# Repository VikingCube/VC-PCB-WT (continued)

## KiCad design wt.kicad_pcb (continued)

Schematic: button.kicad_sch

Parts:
C11: C-100nF-0805; C_0805_2012Metric_Pad1.18x1.45mm_HandSolder
R30: R-100-0603; R_0603_1608Metric
R31: R-10k-0603; R_0603_1608Metric_Pad0.98x0.95mm_HandSolder
SW2: SW_Push; SW_PUSH_6mm_H9.5mm

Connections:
+3.3VA: R31.1; also elsewhere on the board
BTN0: C11.1, R30.2; also elsewhere on the board
GND3: C11.2, SW2.2; also elsewhere on the board
unnamed: R30.1, R31.2, SW2.1

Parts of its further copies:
C10, C12, C13, C14, C15: C-100nF-0805; C_0805_2012Metric_Pad1.18x1.45mm_HandSolder
R13, R38, R40, R42, R44: R-100-0603; R_0603_1608Metric
R14, R39, R41, R43, R45: R-10k-0603; R_0603_1608Metric_Pad0.98x0.95mm_HandSolder
SW1, SW3, SW4, SW5, SW6: SW_Push; SW_PUSH_6mm_H9.5mm

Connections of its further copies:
+3.3VA: R14.1, R39.1, R41.1, R43.1, R45.1; also elsewhere on the board
BTN1: C10.1, R13.2; also elsewhere on the board
BTN2: C12.1, R38.2; also elsewhere on the board
BTN3: C13.1, R40.2; also elsewhere on the board
BTN4: C14.1, R42.2; also elsewhere on the board
BTN5: C15.1, R44.2; also elsewhere on the board
GND3: C10.2, C12.2, C13.2, C14.2, C15.2, SW1.2, SW3.2, SW4.2, SW5.2, SW6.2; also elsewhere on the board
unnamed: R13.1, R14.2, SW1.1
unnamed: R38.1, R39.2, SW3.1
unnamed: R40.1, R41.2, SW4.1
unnamed: R42.1, R43.2, SW5.1
unnamed: R44.1, R45.2, SW6.1

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
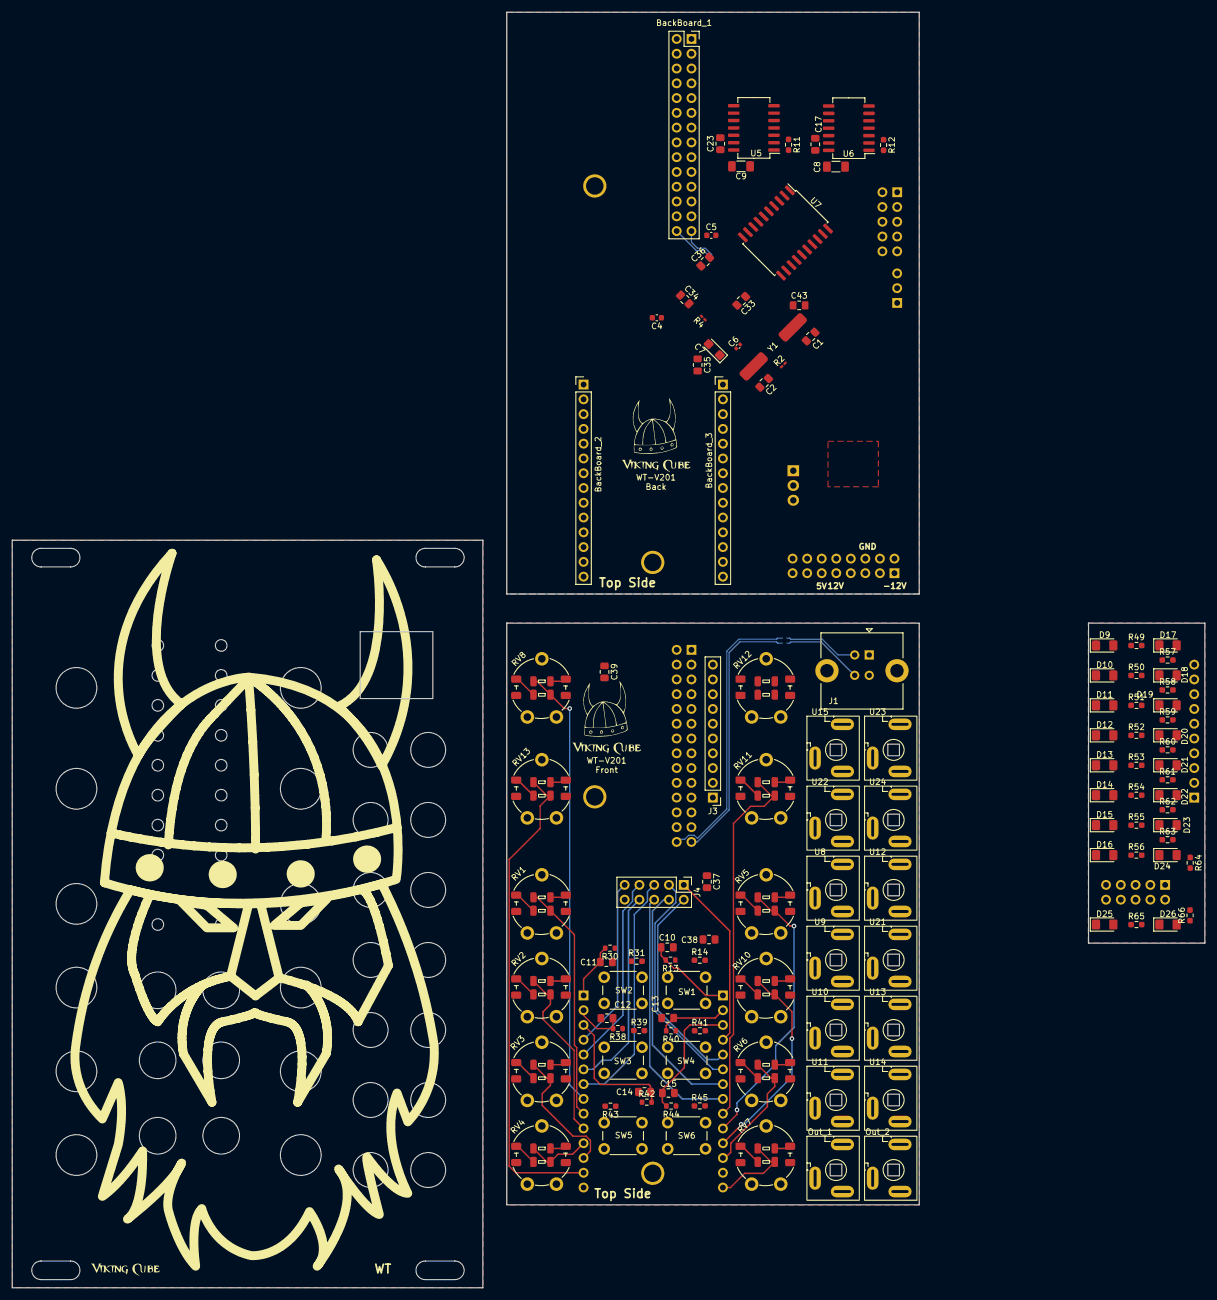
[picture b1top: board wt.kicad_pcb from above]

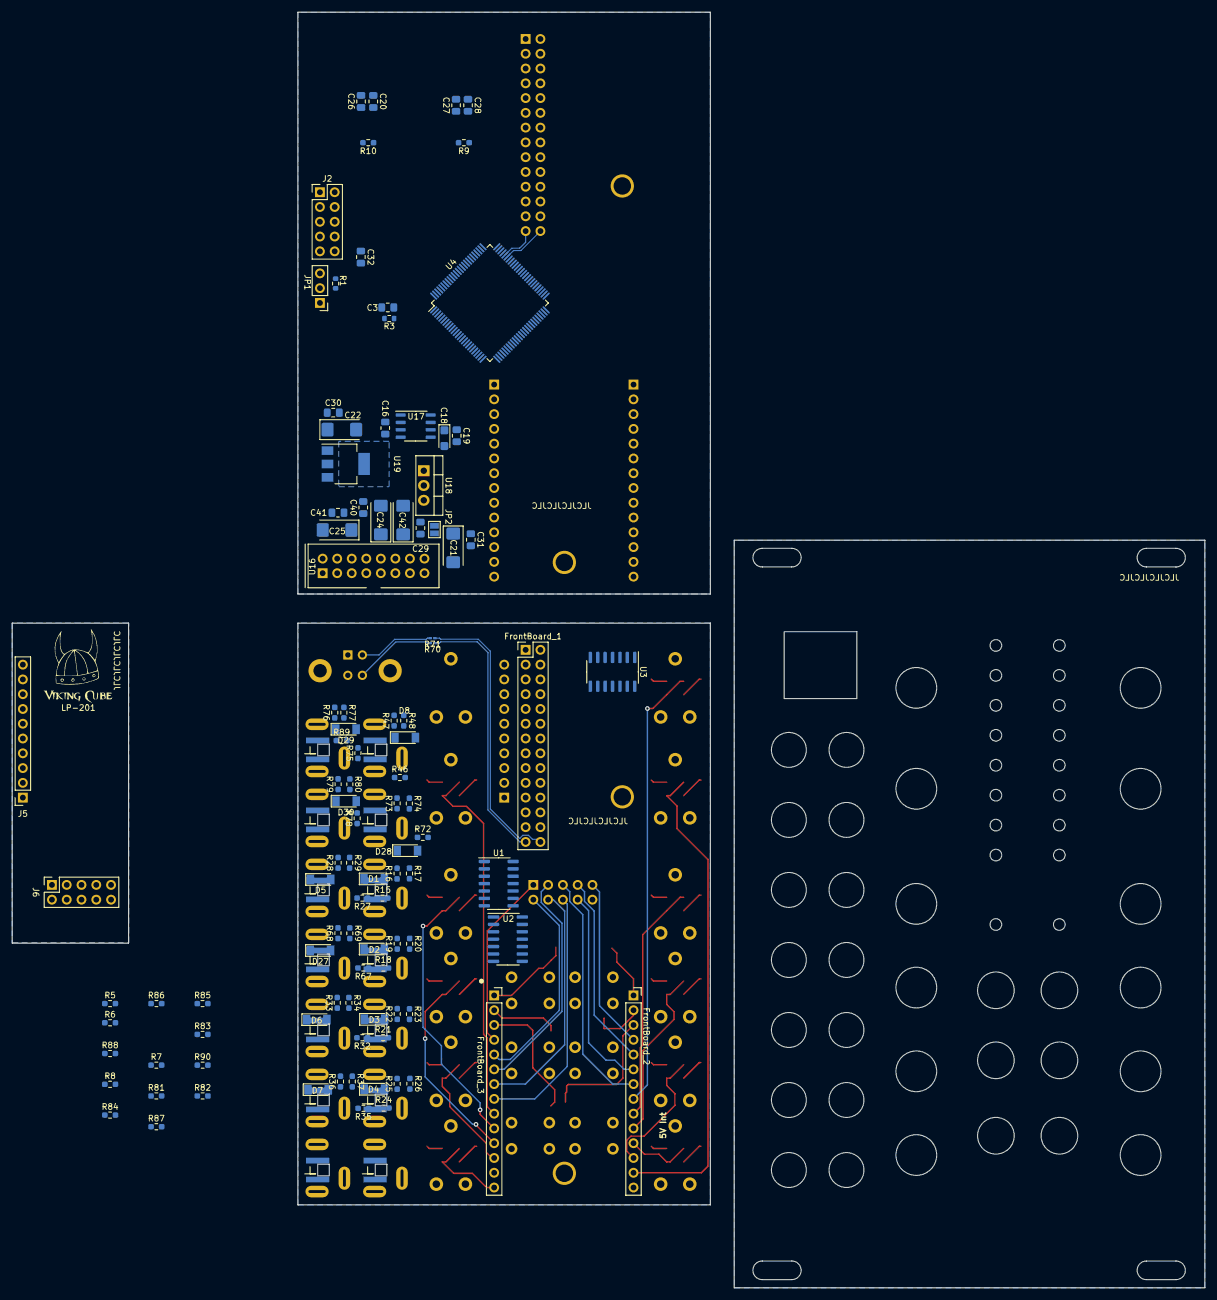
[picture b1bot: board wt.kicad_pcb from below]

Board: 4 copper layers, 205.0 x 219.2 mm, 286 parts (104 on the bottom side), 296 nets.

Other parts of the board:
FP3, FP4, FP5, FP6, FP7, FP8, FP32, FP33, FP34, FP35, FP36, FP37: mount_Potentiometer_Piher_PT-10-V10_Vertical
FP9, FP10, FP11, FP12, FP13, FP14, FP15, FP15#2, FP17#2, FP20, FP21, FP22, FP23, FP24, FP25, FP26, FP27, FP28: mount_m2
FP17, FP18, FP19, FP29, FP30, FP31: mount_SW_PUSH_6mm_H9.5mm
FP38, FP39, FP40, FP41, FP42, FP43, FP44, FP45, FP46, FP47, FP48, FP49, FP50, FP51: mount_LUM_1502-03
FP54: mount_USB-BG
FP55: JLCPCB-TAG
G011: LOGO; logo_small
LOGO: logo_head
Mount4: mount_m3_pad
Mount_1, Mount_2: mount_m3_pad
REF123: JLCPCB-TAG
TEXT1, TEXT2: JLCPCB-TAG
mount3: mount_m3_pad
mount_1, mount_2, mount_3, mount_4: mounting

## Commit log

2022-07-29 First
2022-07-29 working on the schema
2022-07-29 started to work on power part
2022-07-31 working on powers
2022-07-31 refactoring with global labels
2022-08-01 cleaning into modules
2022-08-02 Working on the limiter
2022-08-03 working on AD inputs
2022-08-04 re-thinked the controls
2022-08-04 added some missing wires, whoopppssssz
2022-08-04 reannotated changed to LM324
2022-08-04 almost messed up the opamp :)
2022-08-05 Made the first proposed layout
2022-08-14 working on the PCB
2022-08-14 working on PCB
2022-08-15 PCV WIP
2022-08-15 fixed aligments - check again
2022-08-20 working on PCB, new iteratrion
2022-08-30 Working on the PCB / JTAG
2022-09-01 started to pull GND
2022-09-01 shall be error free, proceeding to warnings
2022-09-01 no more warnings making it nicer
2022-09-01 Added the logo
2022-09-01 Added some labels
2022-09-05 final touches
2022-09-27 reworking with Pot Lights
2022-09-30 fixed issues, power still needs to be addressed
2022-10-04 New design
2022-10-09 working on the new pcb
2022-10-10 working on PCB v2 LEDs
2022-10-10 using power plane as signal too - will this fly?
2022-10-10 Moved around a lot, I think we close to GND phase
2022-10-11 Getting into GND-ing
2022-10-12 grounding
2022-10-14 v2 error free
2022-10-14 V2.0 final
2022-10-14 Working on the cover
2022-10-18 working on lifted leds
2022-10-18 wip led panel
2022-10-18 working on v3 - todo go on with power lines
2022-10-18 wip - go btn
2022-10-21 working on the v3 leds
2022-10-21 woking on the LEDs
2022-10-26 yet an other new version with 3 boards
2022-10-26 this will be a monster
2022-10-27 working on v3 - so far so good
2022-10-27 wip v3
2022-10-31 v4 error free
2022-10-31 v4 grounding
2022-10-31 Final V4, no cover
2022-10-31 V4 cover wip
2022-10-31 V4 with Cover, final?
2022-10-31 V4 - Final
2022-10-31 removed other panels
2022-10-31 fixed jlc tag
2022-11-17 fixed button hole size on front panel
2022-11-25 updated readme.
2022-11-26 fixed hole sizes
2022-12-02 Fixed the button positions, right side was 0.5mm off
2022-12-02 Modified front panel to v005 - needs new tags for front and cover!
2022-12-06 fixed mounting holes
2023-12-01 added docs for github website
2023-12-01 removed doc, updated for kicad 7.0
2023-12-02 Kicad version update
2023-12-03 Changed all R to 0603
    all res to 0603 and changed JACK to LED Jack (for fancy)
2023-12-03 working on the new version,
